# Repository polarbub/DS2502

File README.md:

# Arduino based DS2502 controller

The DS2502 is a 1024bit add-only EPROM. You can add data but cannot change it. It is used mainly for device identification purposes like serial number, manufacturer data, unique identifiers, Dell Laptop Power supplies, etc. It uses the Maxim 1-wire bus. This repository is kind of like a multitool for DS2502s. It lets you read, write, check the status, and check the ID of these chips and all with a (fairly) intuitive interface. If you have any issues or questions feel free to make a GitHub issue.

When cloning this repository make sure to also clone the submodules by using `git clone --recursive`. This repository has a submodule for the OneWire library and one for the Arduino core. Both are for the CMake build system.

## Software
There are two ways to build the software. The first one is as a normal Arduino sketch. To use it open `software/src/src.ino` in the Arduino IDE and upload. Make sure to have the [OneWire library](https://www.arduino.cc/reference/en/libraries/onewire/) installed. The second way is with CMake. This method was made to allow the software to be written in IDEs other than the Arduino IDE. It probably won't build on platforms other than Linux and it definitely won't work for anything other than a Arduino Uno, but could be adapted easily to fix either of those issues.

The software will only work with LF line endings. It will not work with CR or CRLF line endings. This is the default in the Arduino IDE serial monitor, but in other programs it is not. To connect using picocom for example run `picocom -b 9600 --omap crlf --imap lfcrlf /dev/ttyACM<number>`

This program, unlike many others, does read the identification rom of the DS2502, so it will give a comprehensive error when it finds a device that is not a DS2502 instead of a CRC one. This also allows it to handle having multiple DS2502s on the same OneWire bus.

The software has two main limitations. It doesn't support writing to the status register or crc checks on subsequent writes. Adding support for the former would be relatively simple, but I can't find an example of where the latter works.

If you get a CRC error where the DS2052 CRC is FF then it likely means that the DS2502 was disconnected. This is because the OneWire bus is pulled up to a logical 1 and if there is no DS2502 to bring it to ground it will read 0xFF (0b11111111).

## Hardware
The programmer schematic in the hardware folder is just a copy of the first circuit of figure 8 in the [DS2502 datasheet](https://www.analog.com/media/en/technical-documentation/data-sheets/DS2502.pdf). The PCB is just a layed out version of the programmer. The arduino schematic shows how to hook up an Arduino to a DS2502 for reading only.

Pin 6 on the Arduino is the OneWire pin and pin 7 is the programming one.

If you are trying to order a DS2502, but can't find any a DS2502+ is functionally equivalent.

## Simulator

For ease of testing there is a simulator file included for [SimulIDE](https://simulide.com/p/). This simulator uses three Arduino Unos. One runs this software and the other two run [OneWireHub](https://github.com/orgua/OneWireHub)'s DS2502 emulator example sketch. This library is and Arduino library and can be found in the IDE library manager. OneWireHub does have some issues though. Writing to it having multiple devices on the same bus both don't work. The former issue is reported [here](https://github.com/orgua/OneWireHub/issues/137). Real hardware is required to test those functions.

The best way I found to get access to the serial console of the Arduino in SimulIDE was to use the Serial Port and socat to loop it back to a serial terminal. To set this up run  
1. `socat -d -d pty,raw,echo=0 pty,raw,echo=0`
2. `picocom -b 9600 --omap crlf --imap lfcrlf /dev/pts/<pts one from socat>`
3. `sudo simulide`
4. Open the circuit
5. Open the serial port properties and put `/dev/pts/<pts two from socat>` in there
6. Press open on the serial port

## Useful Links

There are many useful resources that I used to complete this project. Here are a few of them
- https://github.com/orgua/OneWireHub/blob/main/examples/DS2502_DELLCHG/readme.md
- https://github.com/orgua/OneWireHub/blob/main/examples/DS2502_DELLCHG/DS2502_DELLCHG.ino
- https://github.com/KivApple/dell-charger-emulator
- https://github.com/garyStofer/DS2502_DELL_PS
- https://nickschicht.wordpress.com/2009/07/15/dell-power-supply-fault/
- https://web.archive.org/web/20171231075131/http://www.laptop-junction.com/toast/content/dell-ac-power-adapter-not-recognized

## License 
Everything except the software folder is licensed under Creative Commons Attribution-ShareAlike 4.0 International
The software folder is licensed under the GPLv3

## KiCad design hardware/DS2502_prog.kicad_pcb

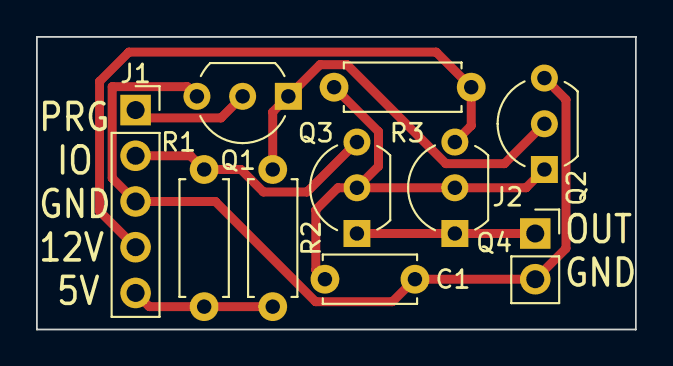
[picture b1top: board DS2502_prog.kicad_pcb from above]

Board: 2 copper layers, 33.3 x 16.3 mm, 10 parts (0 on the bottom side), 8 nets.

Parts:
C1: 470 pF; C_Disc_D5.0mm_W2.5mm_P5.00mm
J1: Conn_01x05_Socket; PinSocket_1x05_P2.54mm_Vertical
J2: Conn_01x02_Socket; PinSocket_1x02_P2.54mm_Vertical
Q1, Q2, Q3: 2N7000; TO-92_Inline_Wide
Q4: VP0106N3; TO-92_Inline_Wide
R1: 4.7K; R_Axial_DIN0207_L6.3mm_D2.5mm_P7.62mm_Horizontal
R2: 10k; R_Axial_DIN0207_L6.3mm_D2.5mm_P7.62mm_Horizontal
R3: 10K; R_Axial_DIN0207_L6.3mm_D2.5mm_P7.62mm_Horizontal

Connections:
+5V: J1.5, R1.2, R2.2
+12V: J1.4, Q4.3 (S), R3.2
/Programmer/DS2502: J2.1, Q3.1 (D), Q4.1 (D)
/Programmer/IO: J1.2, Q3.3 (S), R1.1
/Programmer/PRGM: J1.1, Q1.2 (G)
GND: C1.2, J1.3, J2.2, Q1.3 (S), Q2.3 (S)
unnamed: Q1.1 (D), Q2.2 (G), R2.1
unnamed: C1.1, Q2.1 (D), Q3.2 (G), Q4.2 (G), R3.1

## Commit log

2024-05-30 Reading works
2024-05-30 Rom works?
2024-05-31 Before CRC
2024-05-31 First writing revision
2024-06-06 Before adding starting write starting address
2024-06-09 before removing main
2024-06-10 Restructuring and add submodules
2024-06-10 Fix the hardware folder, finish readme, and clean up
2024-06-10 Fix readme
2024-06-11 Fix CRC issues
2024-06-12 Add note about CRC errors
